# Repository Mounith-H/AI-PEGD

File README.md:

# AI Powered Edge-Based Gunshot Detection for Protecting Wildlife

This repository contains the complete implementation of an AI-powered edge-based gunshot detection system designed for wildlife protection. The project combines machine learning, hardware implementation, and real-time audio processing to detect gunshots in wildlife environments.

## Repository Structure

### `hardware/`
Contains hardware-related files, logs, and performance metrics for the edge device implementation.

#### `hardware/LOG/`
- `Receiver_node_log.txt` - Log file for the receiver node operations and data transmission
- `Sensor_node_log.txt` - Log file for the sensor node audio capture and preprocessing

#### `hardware/Enclosure`
Directory containing test results for the physical enclosure.

- `Axial force displace.xlsx` - Excel file documenting axial force displacement test results.
- `S-N test.xlsx` - Excel file documenting S-N (Stress-Number) test results.
- `tension test.xlsx` - Excel file documenting tension test results.

### `ML/`
Contains all machine learning related files including datasets, training scripts, models, and performance analysis.

#### `ML/dataset/`
Audio dataset used for training and testing the gunshot detection model.

- `environment_audio/` - Directory containing environmental/background audio samples (non-gunshot sounds)
- `gunshots_audio/` - Directory containing gunshot audio samples for training

#### `ML/figures_data/`
CSV files containing data used to generate performance plots and visualizations.

**Accuracy Plot Data:**
- `accuracy_plot_data__400.csv` - Training/validation accuracy data for 400-sample dataset
- `accuracy_plot_data__1000.csv` - Training/validation accuracy data for 1000-sample dataset
- `accuracy_plot_data__1700.csv` - Training/validation accuracy data for 1700-sample dataset
- `accuracy_plot_data__2000.csv` - Training/validation accuracy data for 2000-sample dataset

**Confusion Matrix Data:**
- `confusion_matrix_data__400.csv` - Confusion matrix results for 400-sample dataset
- `confusion_matrix_data__1000.csv` - Confusion matrix results for 1000-sample dataset
- `confusion_matrix_data__1700.csv` - Confusion matrix results for 1700-sample dataset
- `confusion_matrix_data__2000.csv` - Confusion matrix results for 2000-sample dataset

**Loss Plot Data:**
- `loss_plot_data__400.csv` - Training/validation loss data for 400-sample dataset
- `loss_plot_data__1000.csv` - Training/validation loss data for 1000-sample dataset
- `loss_plot_data__1700.csv` - Training/validation loss data for 1700-sample dataset
- `loss_plot_data__2000.csv` - Training/validation loss data for 2000-sample dataset

#### `ML/metrics/`
Comprehensive performance metrics and statistical analysis results.

**Complete Study Metrics:**
- `complete_study_metrics__400.json` - Complete evaluation metrics for 400-sample study
- `complete_study_metrics__1000.json` - Complete evaluation metrics for 1000-sample study
- `complete_study_metrics__1700.json` - Complete evaluation metrics for 1700-sample study
- `complete_study_metrics__2000.json` - Complete evaluation metrics for 2000-sample study

**Statistical Summaries:**
- `statistical_summary__400.csv` - Statistical summary for 400-sample dataset
- `statistical_summary__1000.csv` - Statistical summary for 1000-sample dataset
- `statistical_summary__1700.csv` - Statistical summary for 1700-sample dataset
- `statistical_summary__2000.csv` - Statistical summary for 2000-sample dataset

**Training History:**
- `training_history_per_epoch__400.csv` - Epoch-wise training history for 400-sample dataset
- `training_history_per_epoch__1000.csv` - Epoch-wise training history for 1000-sample dataset
- `training_history_per_epoch__1700.csv` - Epoch-wise training history for 1700-sample dataset
- `training_history_per_epoch__2000.csv` - Epoch-wise training history for 2000-sample dataset

#### `ML/training/`
Model training scripts and trained model files.

- `model_training_quantization_jupyter.ipynb` - Jupyter notebook for model training and quantization
- `gunshot_model_quant.tflite` - Quantized TensorFlow Lite model for edge deployment

#### `ML/training/exported_models/`
Directory containing exported model files in different formats.

##### `ML/training/exported_models/keras/`
- `gunshot_detection.keras` - Full Keras model file with complete architecture and weights

##### `ML/training/exported_models/quantized/`
- `gunshot_model_quant.tflite` - Quantized TensorFlow Lite model optimized for edge devices

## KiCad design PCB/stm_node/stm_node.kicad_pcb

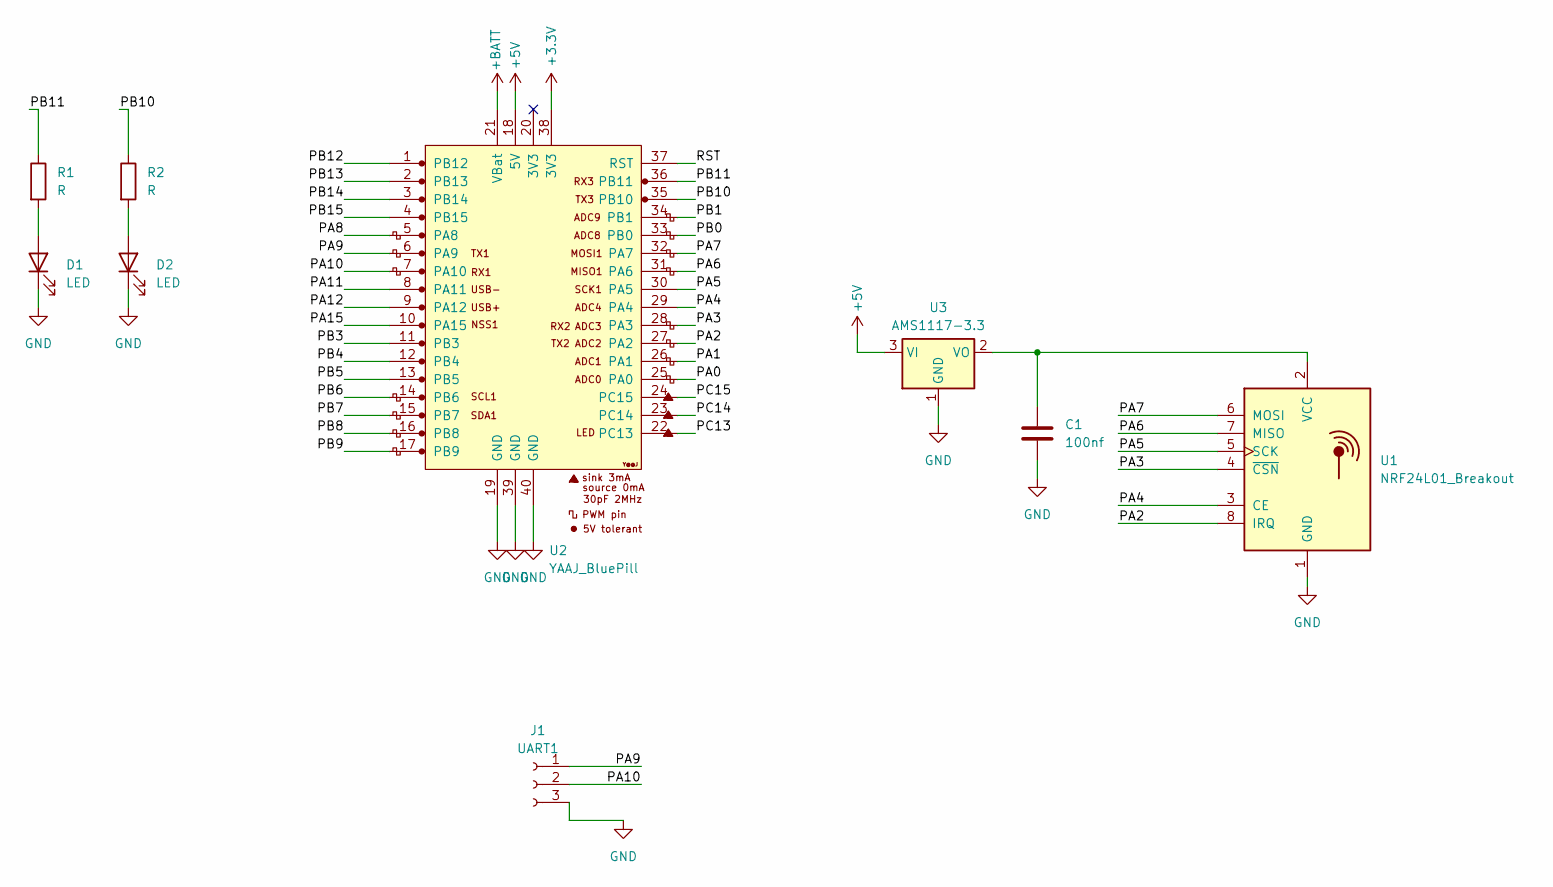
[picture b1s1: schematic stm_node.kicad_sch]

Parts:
C1: 100nf; CP_EIA-3528-12_Kemet-T_HandSolder
D1, D2: LED; LED_D5.0mm
J1: UART1; JST_XH_B3B-XH-A_1x03_P2.50mm_Vertical
R1, R2: R; R_Axial_DIN0207_L6.3mm_D2.5mm_P10.16mm_Horizontal
U1: NRF24L01_Breakout; nRF24L01_Breakout
U2: YAAJ_BluePill; YAAJ_BluePill_1
U3: AMS1117-3.3; SOT-223-3_TabPin2

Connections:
+3.3V: U2.38 (3V3)
+5V: U2.18 (5V), U3.3 (VI)
+BATT: U2.21 (VBat)
/PA0: U2.25 (PA0)
/PA1: U2.26 (PA1)
/PA2: U1.8 (IRQ), U2.27 (PA2)
/PA3: U1.4 (~CSN), U2.28 (PA3)
/PA4: U1.3 (CE), U2.29 (PA4)
/PA5: U1.5 (SCK), U2.30 (PA5)
/PA6: U1.7 (MISO), U2.31 (PA6)
/PA7: U1.6 (MOSI), U2.32 (PA7)
/PA8: U2.5 (PA8)
/PA9: J1.1, U2.6 (PA9)
/PA10: J1.2, U2.7 (PA10)
/PA11: U2.8 (PA11)
/PA12: U2.9 (PA12)
/PA15: U2.10 (PA15)
/PB0: U2.33 (PB0)
/PB1: U2.34 (PB1)
/PB3: U2.11 (PB3)
/PB4: U2.12 (PB4)
/PB5: U2.13 (PB5)
/PB6: U2.14 (PB6)
/PB7: U2.15 (PB7)
/PB8: U2.16 (PB8)
/PB9: U2.17 (PB9)
/PB10: R2.1, U2.35 (PB10)
/PB11: R1.1, U2.36 (PB11)
/PB12: U2.1 (PB12)
/PB13: U2.2 (PB13)
/PB14: U2.3 (PB14)
/PB15: U2.4 (PB15)
/PC13: U2.22 (PC13)
/PC14: U2.23 (PC14)
/PC15: U2.24 (PC15)
/RST: U2.37 (RST)
GND: C1.2, D1.1 (K), D2.1 (K), J1.3, U1.1 (GND), U2.19 (GND), U2.39 (GND), U2.40 (GND), U3.1 (GND)
unnamed: D1.2 (A), R1.2
unnamed: D2.2 (A), R2.2
unnamed: C1.1, U1.2 (VCC), U3.2 (VO)

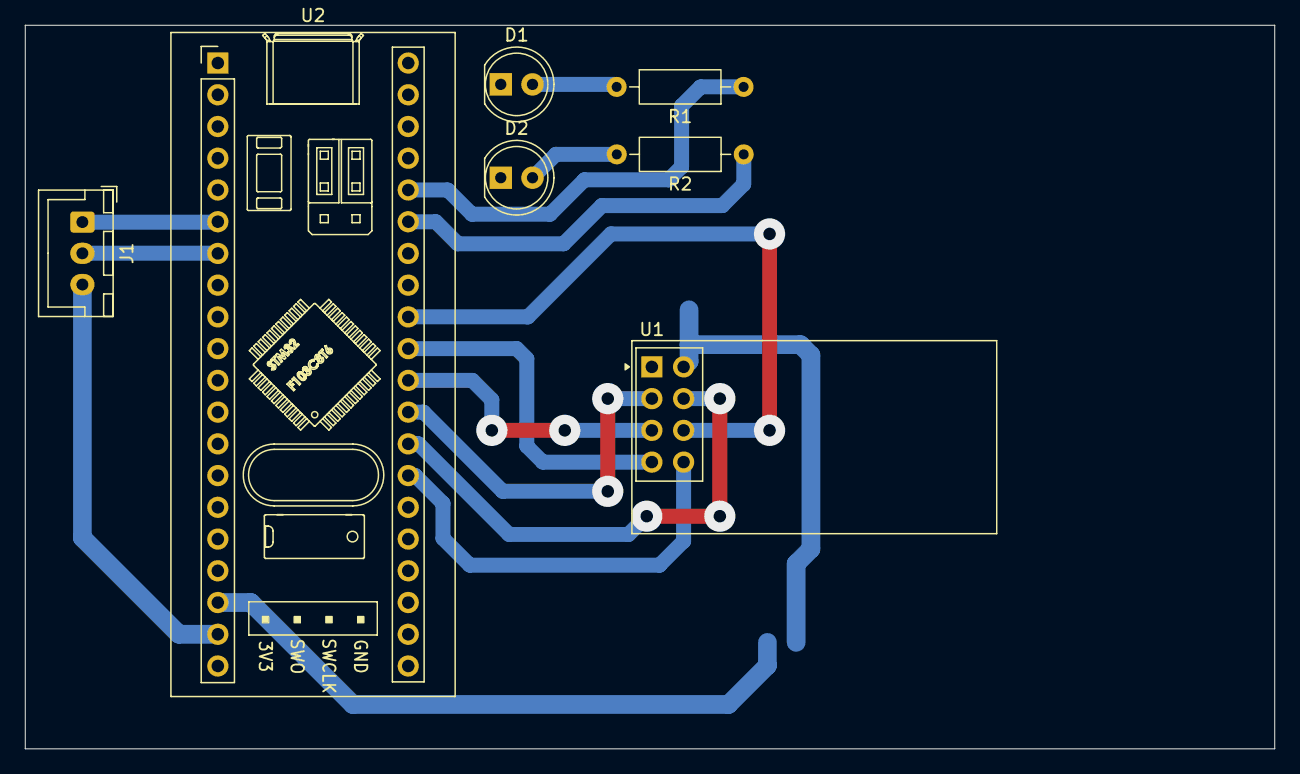
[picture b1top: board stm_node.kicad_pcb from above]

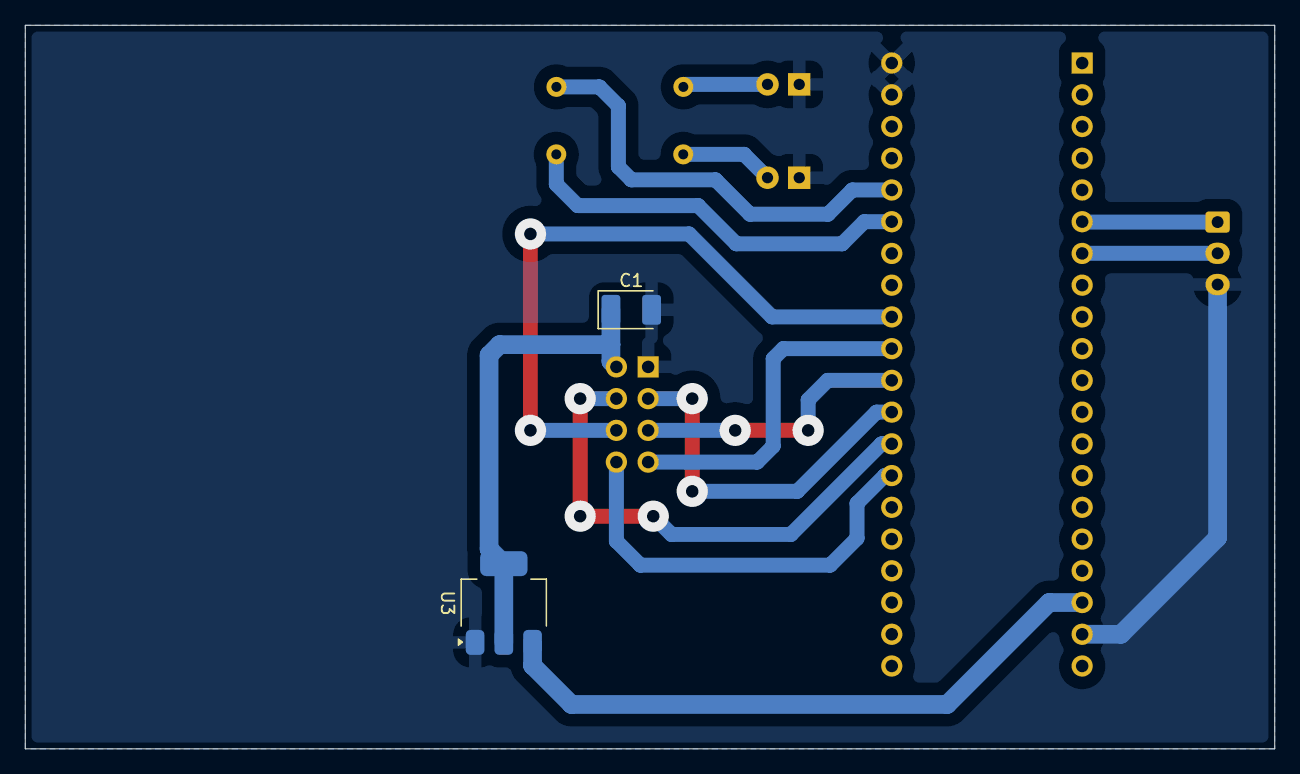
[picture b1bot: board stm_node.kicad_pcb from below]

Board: 2 copper layers, 100.0 x 57.9 mm, 9 parts (2 on the bottom side), 15 nets.

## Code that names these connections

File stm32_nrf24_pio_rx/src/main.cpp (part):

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#include "printf.h"
#include "RF24.h"

#define siran_pin PB10 // Pin for Siran mode
#define LED_PIN PB11 // Pin for LED indication

RF24 radio(PA4, PA3);  // using pin PA4 for the CE pin, and pin PA3 for the CSN pin
// IRQ pin is connected to PA2 but not used in this basic example

// Debug serial on PA9 (TX) and PA10 (RX) - Hardware Serial2
HardwareSerial DebugSerial(PA10, PA9); // RX, TX pins

// Data reconstruction variables
String completeMessage = "";
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
void setup() {
  Serial.begin(115200);      // USB Serial - for JSON output only
  DebugSerial.begin(115200); // Debug Serial on PA9/PA10 - for debug messages
  
  pinMode(PC13, OUTPUT); // LED pin for indication
  pinMode(siran_pin, OUTPUT); // Siran mode pin
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  
  DebugSerial.println("NRF24L01 Receiver Test");
  DebugSerial.println("Pin Configuration:");
  DebugSerial.println("CE  -> PA4");
  DebugSerial.println("CSN -> PA3"); 
  DebugSerial.println("SCK -> PA5");
  DebugSerial.println("MOSI-> PA7");
  DebugSerial.println("MISO-> PA6");
  DebugSerial.println("IRQ -> PA2 (not used)");
  DebugSerial.println("DEBUG TX -> PA9");
  DebugSerial.println("DEBUG RX -> PA10");
  
  // Print radio configuration details
  DebugSerial.println("\nRadio Configuration:");
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  DebugSerial.println("Waiting for incoming transmissions...");
  DebugSerial.println("Expecting messages with 4-byte header + 20-byte data format");
  DebugSerial.println("USB Serial: JSON output only");
  DebugSerial.println("Debug Serial (PA9/PA10): Debug messages");
}  // setup

void loop() {
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
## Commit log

2025-07-03 ML Model added and implemented on pico
2025-07-05 working model
2025-07-18 updated ML model using Edge impulse updated INMP441 pio code
2025-07-18 receiver update
2025-10-07 readme edit
2025-10-23 add ML figures, metrics, models and hardware logs
2025-10-23 images update
